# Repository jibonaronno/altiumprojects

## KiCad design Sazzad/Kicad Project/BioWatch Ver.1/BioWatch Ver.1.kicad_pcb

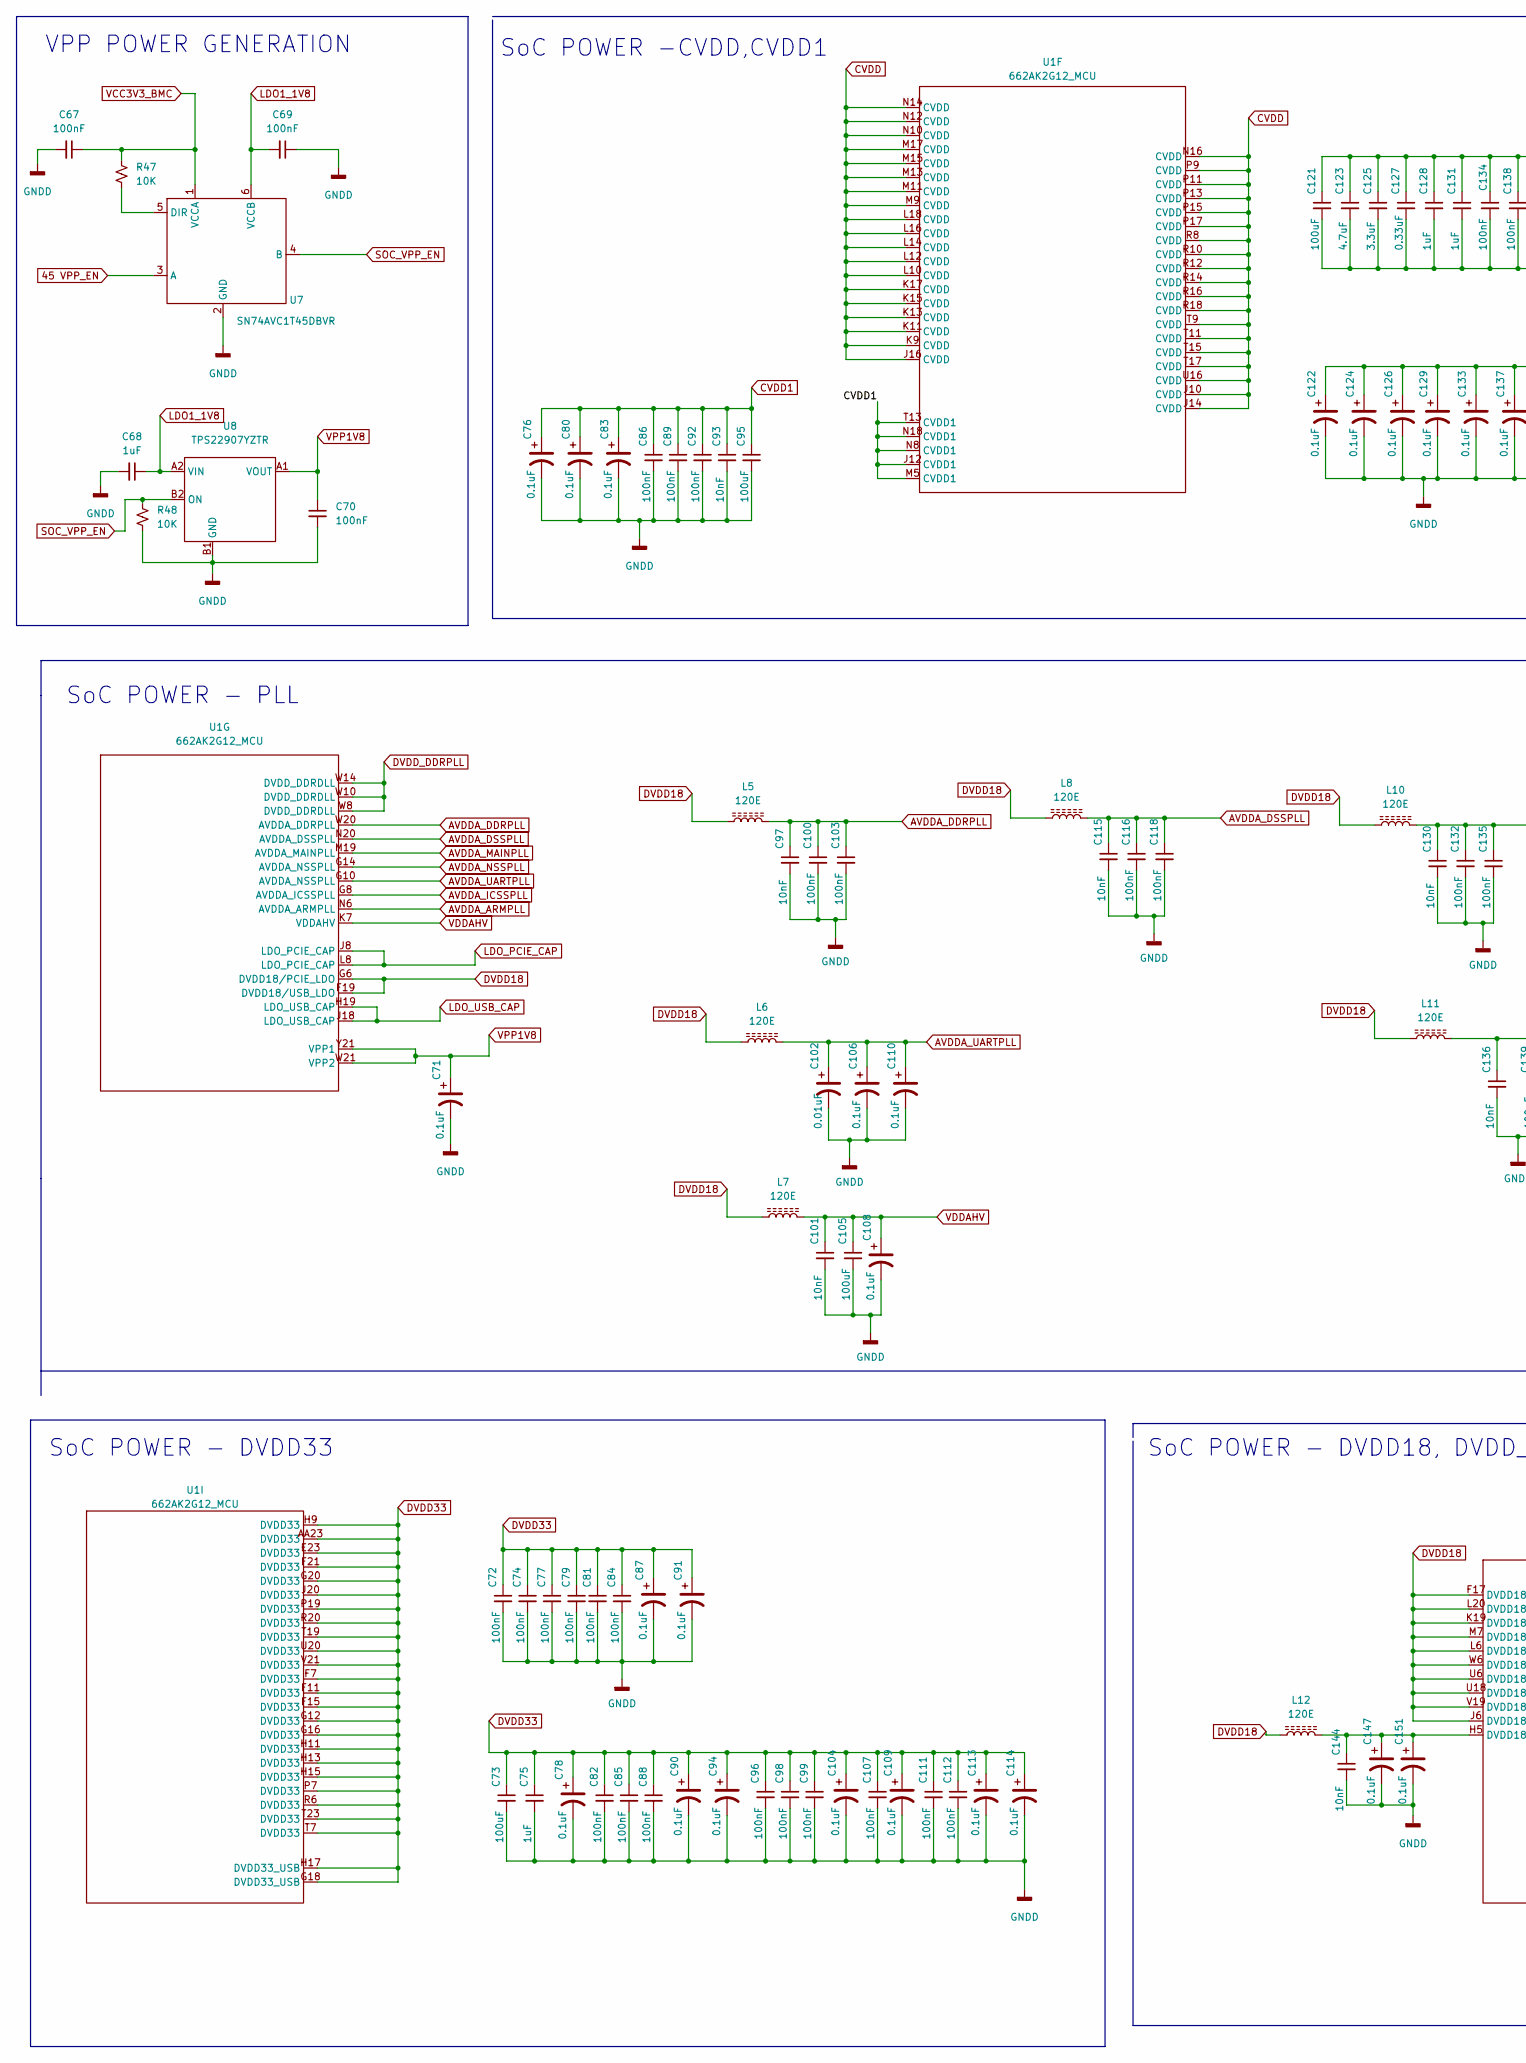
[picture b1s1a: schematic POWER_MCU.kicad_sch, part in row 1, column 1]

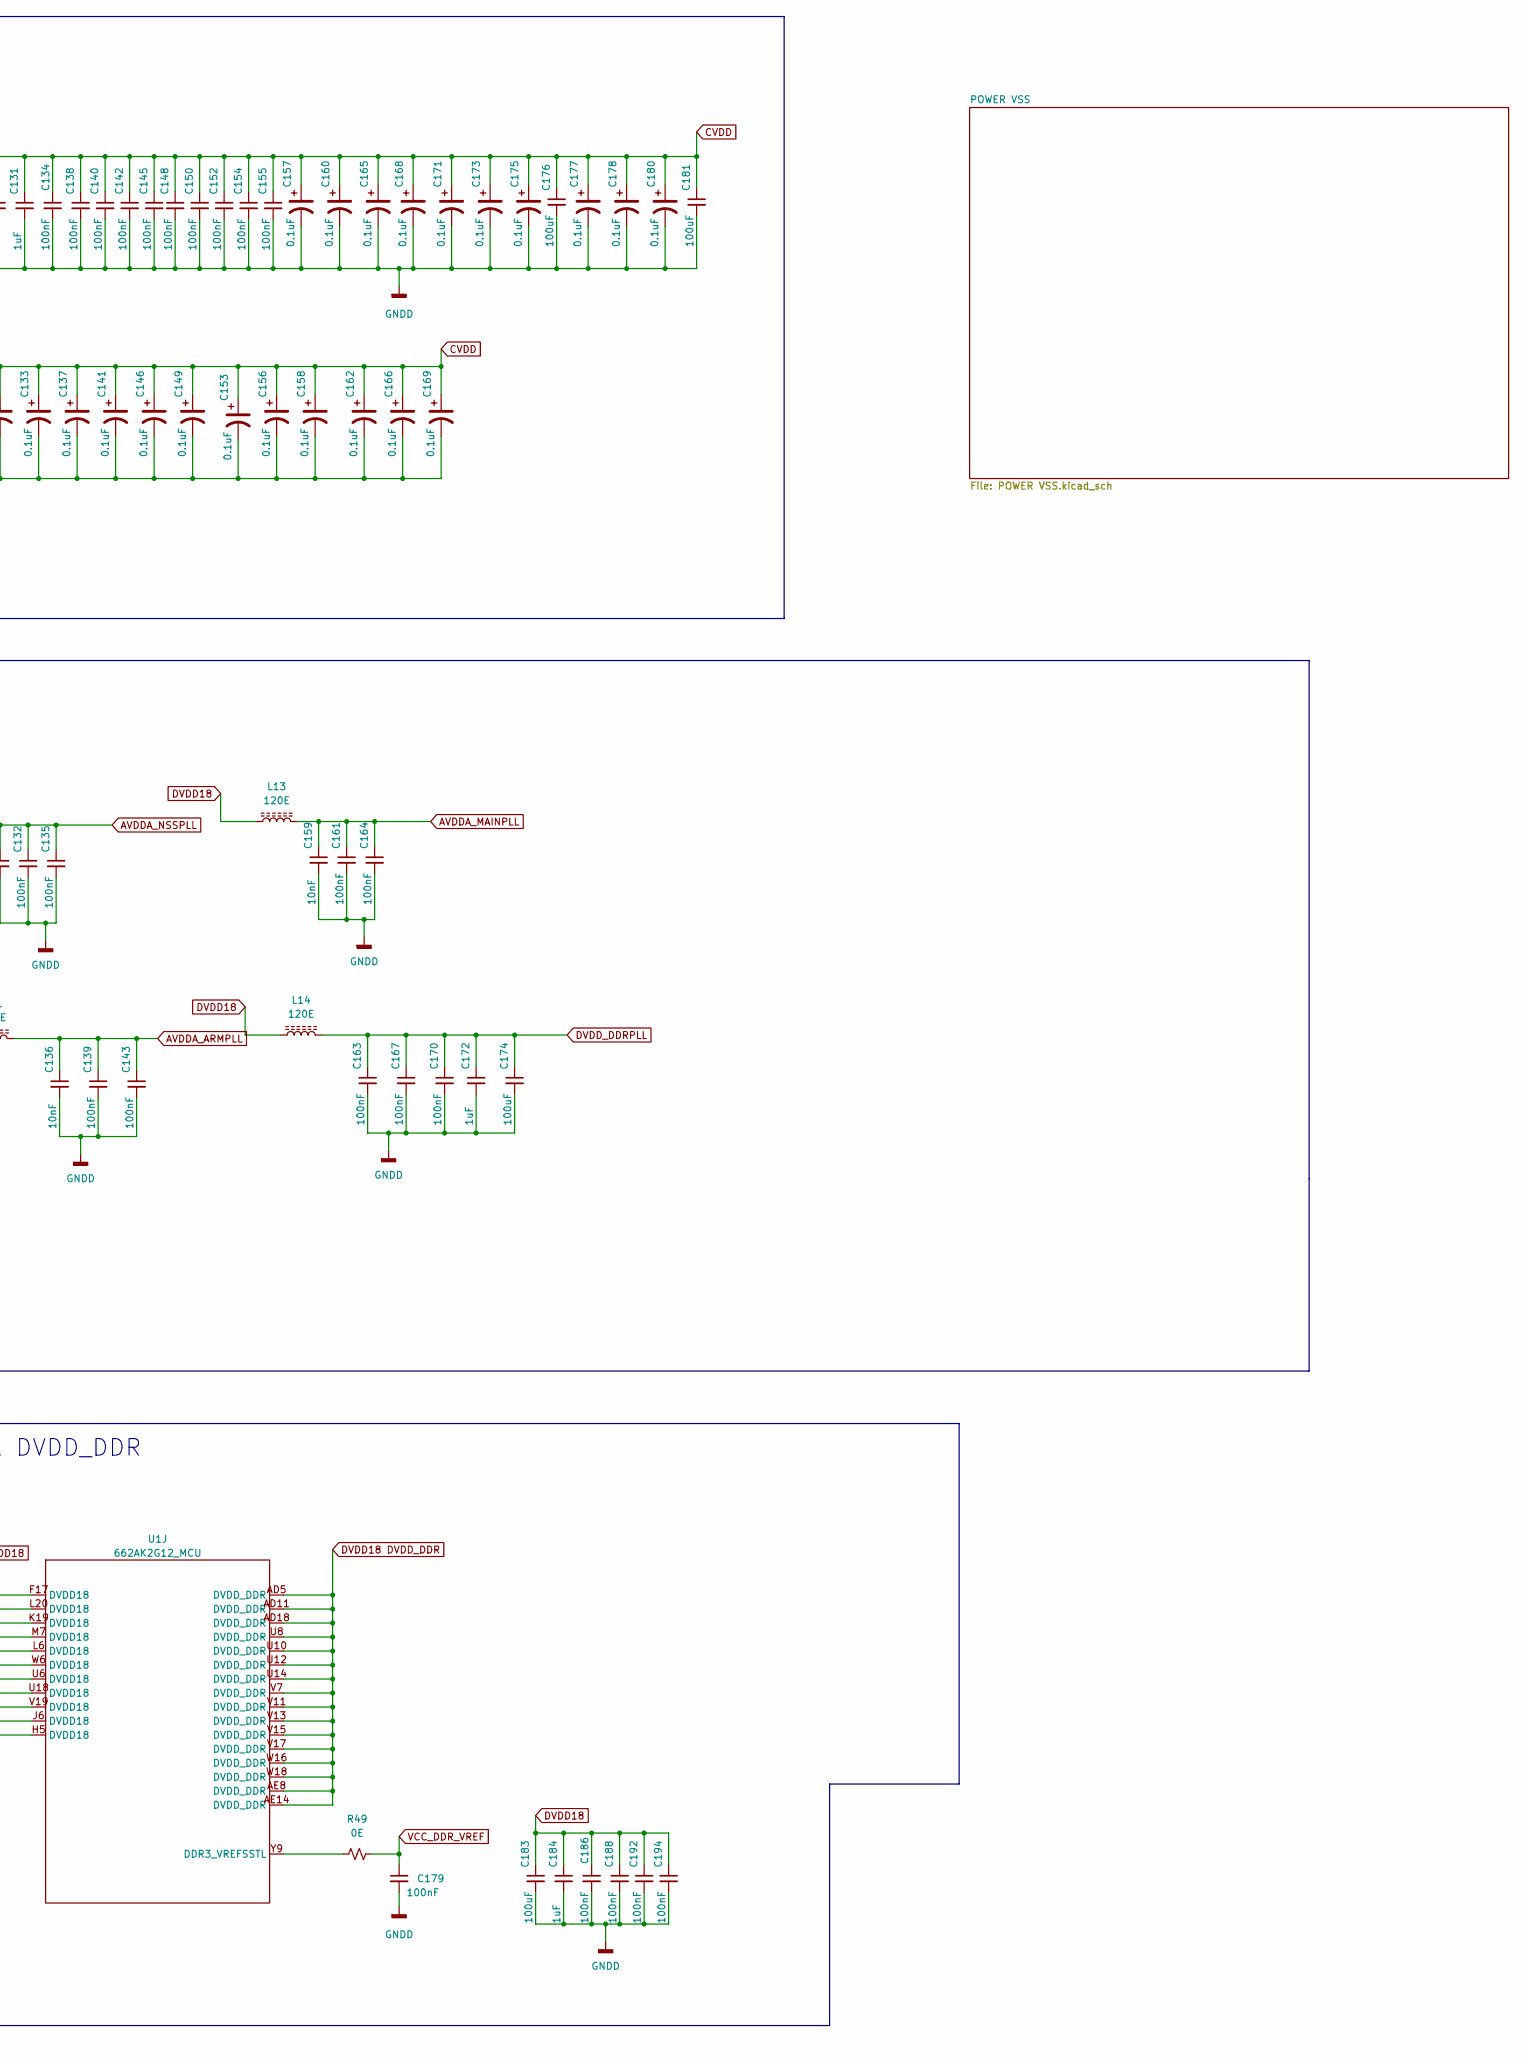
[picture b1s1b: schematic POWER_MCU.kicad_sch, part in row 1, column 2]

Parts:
C67, C69, C70, C72, C74, C77, C79, C81, C82, C84, C85, C86, C88, C89, C92, C96, C98, C99, C100, C103, C107, C111, C112, C116, C118, C132, C134, C135, C138, C139, C140, C142, C143, C145, C148, C150, C152, C154, C155, C161, C163, C164, C167, C170, C179, C186, C188, C192, C194: 100nF; C_0402_1005Metric
C68, C75, C128, C172: 1uF; C_0402_1005Metric
C71, C76, C78, C80, C83, C87, C90, C91, C94, C104, C106, C108, C109, C110, C113, C114, C122, C124, C126, C129, C133, C137, C141, C146, C147, C149, C151, C153, C156, C157, C158, C160, C162, C165, C166, C168, C169, C171, C173, C177, C178, C180: 0.1uF; C_0402_1005Metric
C73, C105, C174, C176, C181, C183: 100uF; CP_Elec_4x3
C93, C97, C101, C115, C130, C136, C144, C159: 10nF; C_0402_1005Metric
C95, C121: 100uF; C_0603_1608Metric
C102: 0.01uF; C_0402_1005Metric
C123: 4.7uF; C_0603_1608Metric
C125: 3.3uF; C_0603_1608Metric
C127: 0.33uF; C_0603_1608Metric
C131, C184: 1uF; C_0603_1608Metric
C175: 0.1uF; C_0603_1608Metric
L5, L6, L7, L8, L10, L11, L12, L13, L14: 120E; L_0805_2012Metric
R47, R48: 10K; R_0603_1608Metric
R49: 0E; R_0603_1608Metric
U1: 662AK2G12_MCU; BGA625
U7: SN74AVC1T45DBVR; SOT-23-6
U8: TPS22907YZTR; SN74AVC1T45DBVR

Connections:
45 VPP_EN: U7.3 (A)
AVDDA_NSSPLL: C130.1, C132.1, C135.1, L10.2
AVDDA_ARMPLL: C136.1, C139.1, C143.1, L11.2, U1.N6 (AVDDA_ARMPLL)
AVDDA_DDRPLL: C97.1, C100.1, C103.1, L5.2, U1.W20 (AVDDA_DDRPLL)
AVDDA_DSSPLL: C115.1, C116.1, C118.1, L8.2, U1.N20 (AVDDA_DSSPLL)
AVDDA_ICSSPLL: U1.G8 (AVDDA_ICSSPLL)
AVDDA_MAINPLL: C159.1, C161.1, C164.1, L13.2, U1.M19 (AVDDA_MAINPLL)
AVDDA_NSSPLL: U1.G14 (AVDDA_NSSPLL)
AVDDA_UARTPLL: C102.1, C106.1, C110.1, L6.2, U1.G10 (AVDDA_NSSPLL)
CVDD: C121.1, C122.1, C123.1, C124.1, C125.1, C126.1, C127.1, C128.1, C129.1, C131.1, C133.1, C134.1, C137.1, C138.1, C140.1, C141.1, C142.1, C145.1, C146.1, C148.1, C149.1, C150.1, C152.1, C153.1, C154.1, C155.1, C156.1, C157.1, C158.1, C160.1, C162.1, C165.1, C166.1, C168.1, C169.1, C171.1, C173.1, C175.1, C176.1, C177.1, C178.1, C180.1, C181.1, U1.J10 (CVDD), U1.J14 (CVDD), U1.J16 (CVDD), U1.K9 (CVDD), U1.K11 (CVDD), U1.K13 (CVDD), U1.K15 (CVDD), U1.K17 (CVDD), U1.L10 (CVDD), U1.L12 (CVDD), U1.L14 (CVDD), U1.L16 (CVDD), U1.L18 (CVDD), U1.M9 (CVDD), U1.M11 (CVDD), U1.M13 (CVDD), U1.M15 (CVDD), U1.M17 (CVDD), U1.N10 (CVDD), U1.N12 (CVDD), U1.N14 (CVDD), U1.N16 (CVDD), U1.P9 (CVDD), U1.P11 (CVDD), U1.P13 (CVDD), U1.P15 (CVDD), U1.P17 (CVDD), U1.R8 (CVDD), U1.R10 (CVDD), U1.R12 (CVDD), U1.R14 (CVDD), U1.R16 (CVDD), U1.R18 (CVDD), U1.T9 (CVDD), U1.T11 (CVDD), U1.T15 (CVDD), U1.T17 (CVDD), U1.U16 (CVDD); also elsewhere on the board
CVDD1: C76.1, C80.1, C83.1, C86.1, C89.1, C92.1, C93.1, C95.1, U1.J12 (CVDD1), U1.M5 (CVDD1), U1.N8 (CVDD1), U1.N18 (CVDD1), U1.T13 (CVDD1)
DVDD18: C183.1, C184.1, C186.1, C188.1, C192.1, C194.1, L5.1, L6.1, L7.1, L8.1, L10.1, L11.1, L12.1, L13.1, L14.1, U1.F17 (DVDD18), U1.F19 (DVDD18/USB_LDO), U1.G6 (DVDD18/PCIE_LDO), U1.J6 (DVDD18), U1.K19 (DVDD18), U1.L6 (DVDD18), U1.L20 (DVDD18), U1.M7 (DVDD18), U1.U6 (DVDD18), U1.U18 (DVDD18), U1.V19 (DVDD18), U1.W6 (DVDD18)
DVDD18 DVDD_DDR: U1.AD5 (DVDD_DDR), U1.AD11 (DVDD_DDR), U1.AD18 (DVDD_DDR), U1.AE8 (DVDD_DDR), U1.AE14 (DVDD_DDR), U1.U8 (DVDD_DDR), U1.U10 (DVDD_DDR), U1.U12 (DVDD_DDR), U1.U14 (DVDD_DDR), U1.V7 (DVDD_DDR), U1.V11 (DVDD_DDR), U1.V13 (DVDD_DDR), U1.V15 (DVDD_DDR), U1.V17 (DVDD_DDR), U1.W16 (DVDD_DDR), U1.W18 (DVDD_DDR)
DVDD33: C72.1, C73.1, C74.1, C75.1, C77.1, C78.1, C79.1, C81.1, C82.1, C84.1, C85.1, C87.1, C88.1, C90.1, C91.1, C94.1, C96.1, C98.1, C99.1, C104.1, C107.1, C109.1, C111.1, C112.1, C113.1, C114.1, U1.AA23 (DVDD33), U1.E23 (DVDD33), U1.F7 (DVDD33), U1.F11 (DVDD33), U1.F15 (DVDD33), U1.F21 (DVDD33), U1.G12 (DVDD33), U1.G16 (DVDD33), U1.G18 (DVDD33_USB), U1.G20 (DVDD33), U1.H9 (DVDD33), U1.H11 (DVDD33), U1.H13 (DVDD33), U1.H15 (DVDD33), U1.H17 (DVDD33_USB), U1.J20 (DVDD33), U1.P7 (DVDD33), U1.P19 (DVDD33), U1.R6 (DVDD33), U1.R20 (DVDD33), U1.T7 (DVDD33), U1.T19 (DVDD33), U1.T23 (DVDD33), U1.U20 (DVDD33), U1.V21 (DVDD33)
DVDD_DDRPLL: C163.1, C167.1, C170.1, C172.1, C174.1, L14.2, U1.W8 (DVDD_DDRDLL), U1.W10 (DVDD_DDRDLL), U1.W14 (DVDD_DDRDLL)
GND: C67.2, C68.2, C69.1, C70.2, C71.2, C72.2, C73.2, C74.2, C75.2, C76.2, C77.2, C78.2, C79.2, C80.2, C81.2, C82.2, C83.2, C84.2, C85.2, C86.2, C87.2, C88.2, C89.2, C90.2, C91.2, C92.2, C93.2, C94.2, C95.2, C96.2, C97.2, C98.2, C99.2, C100.2, C101.2, C102.2, C103.2, C104.2, C105.2, C106.2, C107.2, C108.2, C109.2, C110.2, C111.2, C112.2, C113.2, C114.2, C115.2, C116.2, C118.2, C121.2, C122.2, C123.2, C124.2, C125.2, C126.2, C127.2, C128.2, C129.2, C130.2, C131.2, C132.2, C133.2, C134.2, C135.2, C136.2, C137.2, C138.2, C139.2, C140.2, C141.2, C142.2, C143.2, C144.2, C145.2, C146.2, C147.2, C148.2, C149.2, C150.2, C151.2, C152.2, C153.2, C154.2, C155.2, C156.2, C157.2, C158.2, C159.2, C160.2, C161.2, C162.2, C163.2, C164.2, C165.2, C166.2, C167.2, C168.2, C169.2, C170.2, C171.2, C172.2, C173.2, C174.2, C175.2, C176.2, C177.2, C178.2, C179.2, C180.2, C181.2, C183.2, C184.2, C186.2, C188.2, C192.2, C194.2, R48.2, U7.2 (GND), U8.B1 (GND); also elsewhere on the board
LDO1_1V8: C68.1, C69.2, U7.6 (VCCB), U8.A2 (VIN)
LDO_PCIE_CAP: U1.J8 (LDO_PCIE_CAP), U1.L8 (LDO_PCIE_CAP)
LDO_USB_CAP: U1.H19 (LDO_USB_CAP), U1.J18 (LDO_USB_CAP)
unnamed: C144.1, C147.1, C151.1, L12.2, U1.H5 (DVDD18)
unnamed: R47.2, U7.5 (DIR)
unnamed: R49.1, U1.Y9 (DDR3_VREFSSTL)
SOC_VPP_EN: R48.1, U7.4 (B), U8.B2 (ON)
VCC3V3_BMC: C67.1, R47.1, U7.1 (VCCA)
VCC_DDR_VREF: C179.1, R49.2
VDDAHV: C101.1, C105.1, C108.1, L7.2, U1.K7 (VDDAHV)
VPP1V8: C70.1, C71.1, U1.W21 (VPP2), U1.Y21 (VPP1), U8.A1 (VOUT)

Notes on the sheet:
VPP POWER GENERATION
SoC POWER -CVDD,CVDD1
SoC POWER - DVDD18, DVDD_DDR
SoC POWER - PLL
SoC POWER - DVDD33

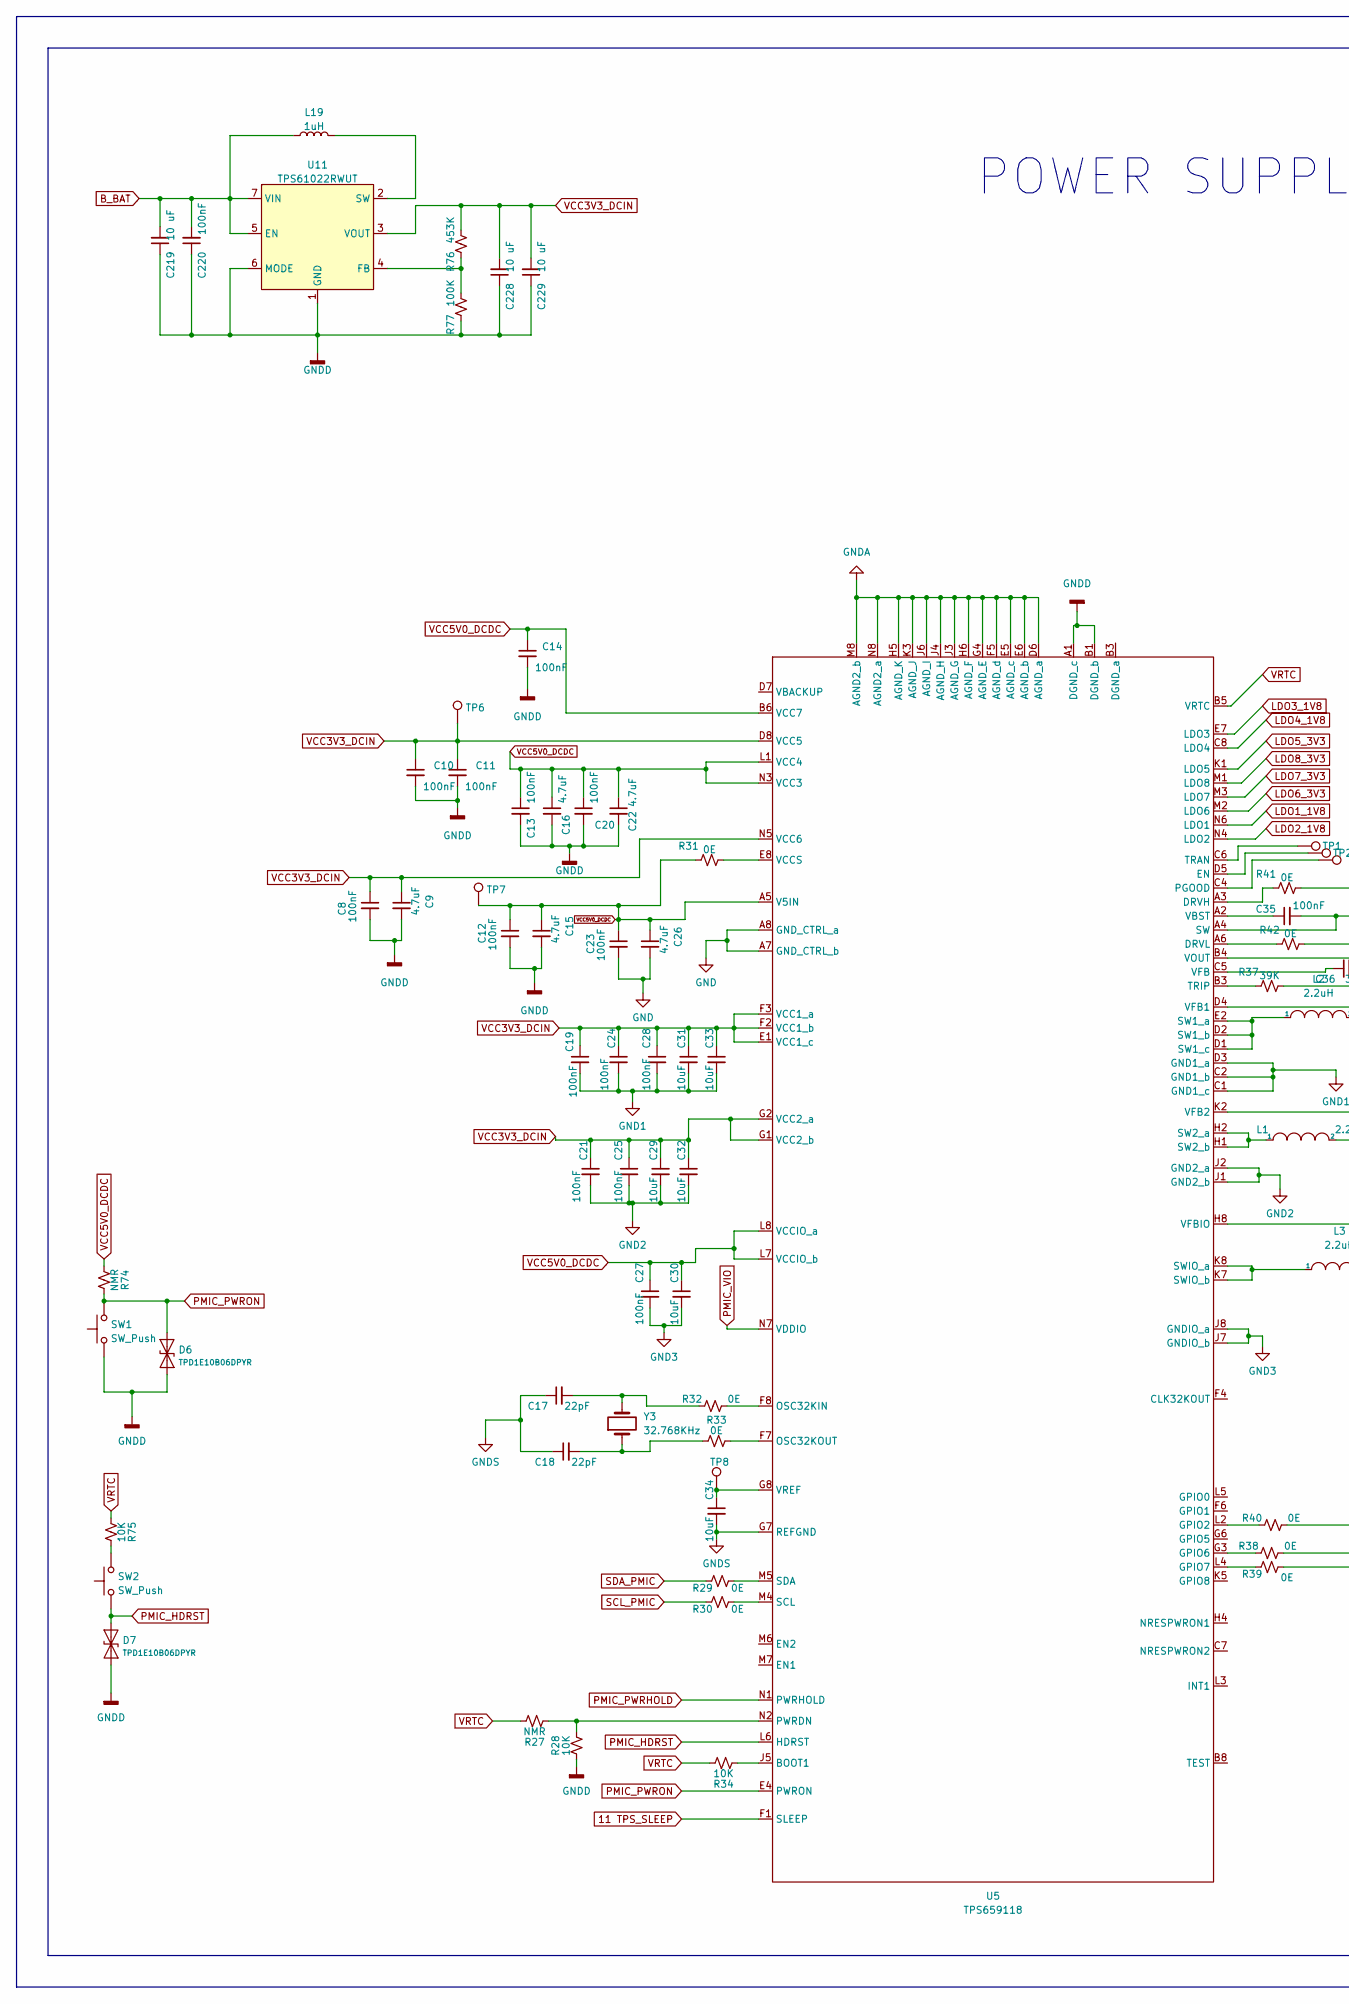
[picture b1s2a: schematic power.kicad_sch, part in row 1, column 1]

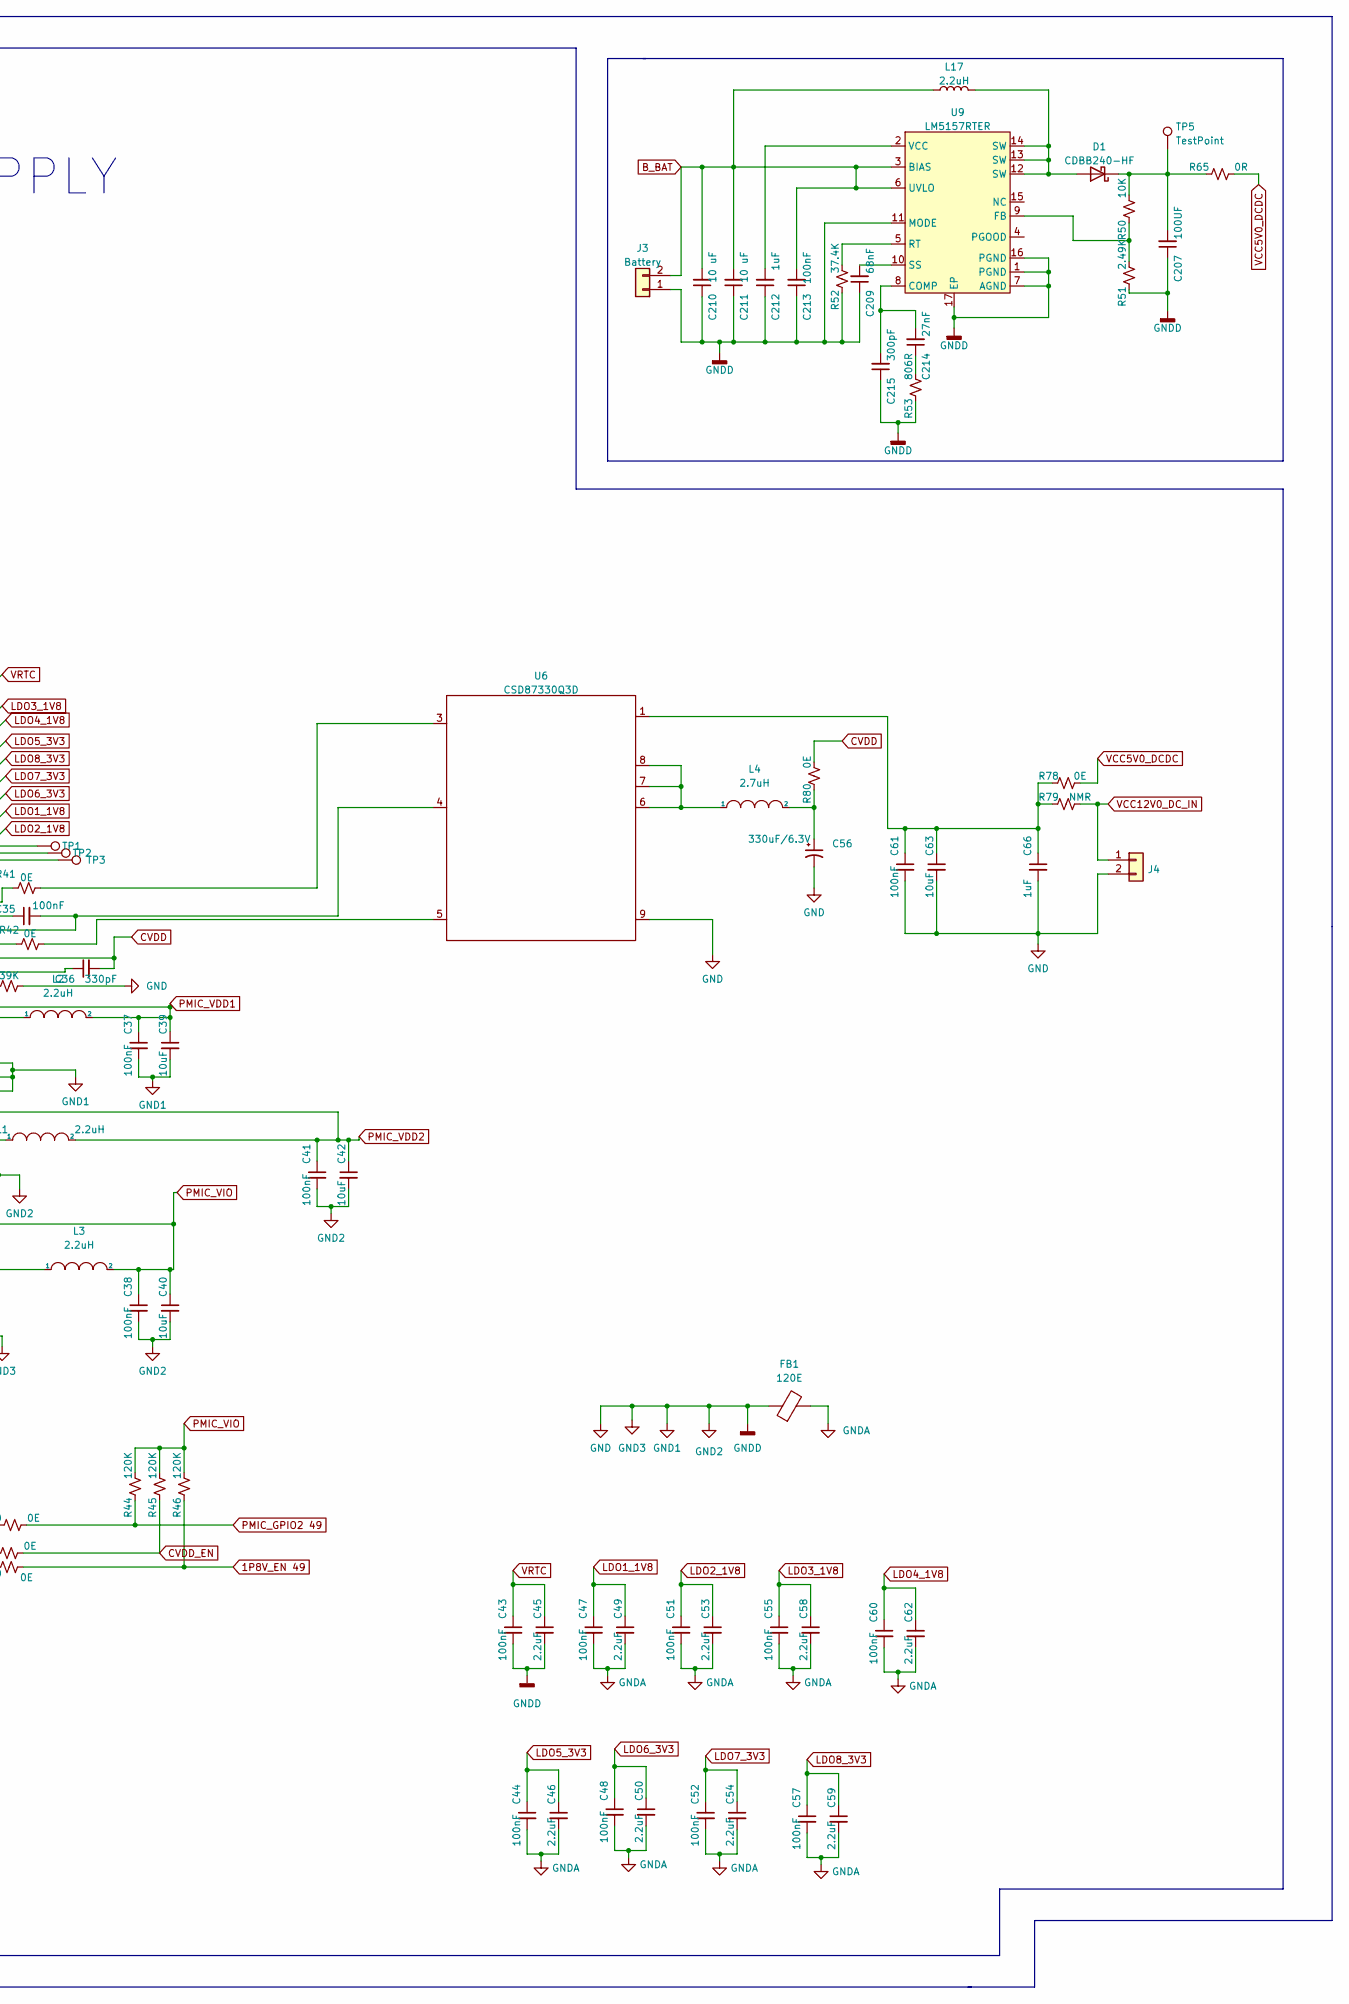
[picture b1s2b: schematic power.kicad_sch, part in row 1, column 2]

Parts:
C8, C10, C11, C12, C13, C14, C19, C20, C21, C23, C24, C25, C27, C28, C35, C37, C38, C41, C43, C44, C47, C48, C51, C52, C55, C57, C60, C61, C213: 100nF; C_0402_1005Metric
C9, C15, C16, C22, C26: 4.7uF; C_0603_1608Metric
C17, C18: 22pF; C_0402_1005Metric
C29, C30, C31, C32, C33, C34, C39, C40, C42, C63: 10uF; C_0603_1608Metric
C36: 330pF; C_0402_1005Metric
C45, C46, C49, C50, C53, C54, C58, C59, C62: 2.2uF; C_0603_1608Metric
C56: 330uF/6.3V; CP_Elec_5x4.5
C66, C212: 1uF; C_0402_1005Metric
C207: 100UF; CP_Elec_5x3
C209: 68nF; C_0402_1005Metric
C210, C211, C219, C228, C229: 10 uF; C_0603_1608Metric
C214: 27nF; C_0402_1005Metric
C215: 300pF; C_0402_1005Metric
C220: 100nF; C_0603_1608Metric
D1: CDBB240-HF; D_SMB
D6, D7: TPD1E10B06DPYR; D_SOD-523
FB1: 120E; R_0603_1608Metric
J3: Battery; JST_EH_B2B-EH-A_1x02_P2.50mm_Vertical
J4: JST_EH_B2B-EH-A_1x02_P2.50mm_Vertical
L1, L2, L3: 2.2uH; L_1210_3225Metric
L4: 2.7uH; L_6.3x6.3_H3
L17: 2.2uH; L_6.3x6.3_H3
L19: 1uH; L_6.3x6.3_H3
R27, R74, R79: NMR; R_0603_1608Metric
R28, R34: 10K; R_0402_1005Metric
R29, R30, R32, R33, R38, R39, R40: 0E; R_0402_1005Metric
R31, R41, R42, R78, R80: 0E; R_0603_1608Metric
R37: 39K; R_0402_1005Metric
R44, R45, R46: 120K; R_0402_1005Metric
R50, R75: 10K; R_0603_1608Metric
R51: 2.49K; R_0603_1608Metric
R52: 37.4K; R_0603_1608Metric
R53: 806R; R_0603_1608Metric
R65: 0R; R_0603_1608Metric
R76: 453K; R_0603_1608Metric
R77: 100K; R_0603_1608Metric
SW1, SW2: SW_Push; SW_Push_1P1T_NO_CK_KMR2
TP1, TP2, TP3, TP5, TP6, TP7, TP8: TestPoint; TestPoint_Pad_D1.0mm
U5: TPS659118; BGA 98
U6: CSD87330Q3D; LSON
U9: LM5157RTER; WQFN-16-1EP_3x3mm_P0.5mm_EP1.6x1.6mm_ThermalVias
U11: TPS61022RWUT; VQFN-7
Y3: 32.768KHz; Crystal_SMD_G8-2Pin_3.2x1.5mm

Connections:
1P8V_EN 49: R39.2, R46.1
11 TPS_SLEEP: U5.F1 (SLEEP)
LDO1_1V8: C47.1, C49.1, U5.N6 (LDO1)
B_BAT: C210.2, C211.2, C213.2, C219.2, C220.2, J3.2, L17.1, L19.1, U9.3 (BIAS), U9.6 (UVLO), U11.5 (EN), U11.7 (VIN)
CVDD: C36.2, R80.2, U5.B4 (VOUT); also elsewhere on the board
CVDD_EN: R38.2, R45.1
GND: C8.2, C9.2, C10.2, C11.2, C12.2, C13.2, C14.2, C15.2, C16.2, C19.2, C20.2, C21.2, C22.2, C23.2, C24.2, C25.2, C26.2, C27.2, C28.2, C29.2, C30.2, C31.2, C32.2, C33.2, C37.2, C38.2, C39.2, C40.2, C41.2, C42.2, C43.2, C45.2, C56.2, C61.2, C63.2, C66.2, C207.1, C209.1, C210.1, C211.1, C212.1, C213.1, C215.1, C219.1, C220.1, C228.1, C229.1, D6.1 (A1), D7.1 (A1), FB1.1, J3.1, J4.2, R28.1, R37.2, R51.1, R52.1, R53.1, R77.1, SW1.1, U5.A1 (DGND_c), U5.A7 (GND_CTRL_b), U5.A8 (GND_CTRL_a), U5.B1 (DGND_b), U5.C1 (GND1_c), U5.C2 (GND1_b), U5.D3 (GND1_a), U5.J1 (GND2_b), U5.J2 (GND2_a), U5.J7 (GNDIO_b), U5.J8 (GNDIO_a), U6.9, U9.1 (PGND), U9.7 (AGND), U9.11 (MODE), U9.16 (PGND), U9.17 (EP), U11.1 (GND), U11.6 (MODE); also elsewhere on the board
GNDA: C44.2, C46.2, C47.2, C48.2, C49.2, C50.2, C51.2, C52.2, C53.2, C54.2, C55.2, C57.2, C58.2, C59.2, C60.2, C62.2, FB1.2, U5.D6 (AGND_a), U5.E5 (AGND_c), U5.E6 (AGND_b), U5.F5 (AGND_d), U5.G4 (AGND_E), U5.H5 (AGND_K), U5.H6 (AGND_F), U5.J3 (AGND_G), U5.J4 (AGND_H), U5.J6 (AGND_I), U5.K3 (AGND_J), U5.M8 (AGND2_b), U5.N8 (AGND2_a)
GNDS: C17.1, C18.1, C34.2, U5.G7 (REFGND)
LDO2_1V8: C51.1, C53.1, U5.N4 (LDO2)
LDO3_1V8: C55.1, C58.1, U5.E7 (LDO3)
LDO4_1V8: C60.1, C62.1, U5.C8 (LDO4)
LDO5_3V3: C44.1, C46.1, U5.K1 (LDO5)
LDO6_3V3: C48.1, C50.1, U5.M2 (LDO6)
LDO7_3V3: C52.1, C54.1, U5.M3 (LDO7)
LDO8_3V3: C57.1, C59.1, U5.M1 (LDO8)
unnamed: C17.2, R32.1, Y3.2
unnamed: C18.2, R33.1, Y3.1
unnamed: C34.1, TP8.1, U5.G8 (VREF)
unnamed: C35.1, U5.A2 (VBST)
unnamed: C35.2, U5.A4 (SW), U6.4
unnamed: C36.1, U5.C5 (VFB)
unnamed: C56.1, L4.2, R80.1
unnamed: C61.1, C63.1, C66.1, R78.1, R79.1, U6.1
unnamed: C207.2, D1.1 (K), R50.2, R65.1, TP5.1
unnamed: C209.2, U9.10 (SS)
unnamed: C212.2, U9.2 (VCC)
unnamed: C214.1, R53.2
unnamed: C214.2, C215.2, U9.8 (COMP)
unnamed: D1.2 (A), L17.2, U9.12 (SW), U9.13 (SW), U9.14 (SW)
unnamed: L1.1, U5.H1 (SW2_b), U5.H2 (SW2_a)
unnamed: L2.1, U5.D1 (SW1_c), U5.D2 (SW1_b), U5.E2 (SW1_a)
unnamed: L3.1, U5.K7 (SWIO_b), U5.K8 (SWIO_a)
unnamed: L4.1, U6.6, U6.7, U6.8
unnamed: L19.2, U11.2 (SW)
unnamed: R27.1, R28.2, U5.N2 (PWRDN)
unnamed: R29.2, U5.M5 (SDA)
unnamed: R30.2, U5.M4 (SCL)
unnamed: R31.2, U5.E8 (VCCS)
unnamed: R32.2, U5.F8 (OSC32KIN)
unnamed: R33.2, U5.F7 (OSC32KOUT)
unnamed: R34.1, U5.J5 (BOOT1)
unnamed: R37.1, U5.B3 (TRIP)
unnamed: R38.1, U5.G3 (GPIO6)
unnamed: R39.1, U5.L4 (GPIO7)
unnamed: R40.1, U5.L2 (GPIO2)
unnamed: R41.1, U5.A3 (DRVH)
unnamed: R41.2, U6.3
unnamed: R42.1, U5.A6 (DRVL)
unnamed: R42.2, U6.5
unnamed: R50.1, R51.2, U9.9 (FB)
unnamed: R52.2, U9.5 (RT)
unnamed: R75.2, SW2.2
unnamed: R76.1, R77.2, U11.4 (FB)
unnamed: TP1.1, U5.C6 (TRAN)
unnamed: TP2.1, U5.D5 (EN)
unnamed: TP3.1, U5.C4 (PGOOD)
PMIC_GPIO2 49: R40.2, R44.1
PMIC_HDRST: D7.2 (A2), SW2.1, U5.L6 (HDRST)
PMIC_PWRHOLD: U5.N1 (PWRHOLD)
PMIC_PWRON: D6.2 (A2), R74.2, SW1.2, U5.E4 (PWRON)
PMIC_VDD1: C37.1, C39.1, L2.2, U5.D4 (VFB1)
PMIC_VDD2: C41.1, C42.1, L1.2, U5.K2 (VFB2)
PMIC_VIO: C38.1, C40.1, L3.2, R44.2, R45.2, R46.2, U5.H8 (VFBIO), U5.N7 (VDDIO)
SCL_PMIC: R30.1; also elsewhere on the board
SDA_PMIC: R29.1; also elsewhere on the board
VCC3V3_DCIN: C8.1, C9.1, C10.1, C11.1, C19.1, C21.1, C24.1, C25.1, C28.1, C29.1, C31.1, C32.1, C33.1, C228.2, C229.2, R76.2, TP6.1, U5.D8 (VCC5), U5.E1 (VCC1_c), U5.F2 (VCC1_b), U5.F3 (VCC1_a), U5.G1 (VCC2_b), U5.G2 (VCC2_a), U5.N5 (VCC6), U11.3 (VOUT); also elsewhere on the board
VCC5V0_DCDC: C12.1, C13.1, C14.1, C15.1, C16.1, C20.1, C22.1, C23.1, C26.1, C27.1, C30.1, R31.1, R65.2, R74.1, R78.2, TP7.1, U5.A5 (V5IN), U5.B6 (VCC7), U5.L1 (VCC4), U5.L7 (VCCIO_b), U5.L8 (VCCIO_a), U5.N3 (VCC3); also elsewhere on the board
VCC12V0_DC_IN: J4.1, R79.2
VRTC: C43.1, C45.1, R27.2, R34.2, R75.1, U5.B5 (VRTC)

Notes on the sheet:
POWER SUPPLY
